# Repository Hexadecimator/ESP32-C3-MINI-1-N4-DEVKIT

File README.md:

# ESP32-C3-MINI-1-N4-DEVKIT
Custom ESP32-C3-MINI-1-N4 board devkit

Rev1 Layout Rendering:

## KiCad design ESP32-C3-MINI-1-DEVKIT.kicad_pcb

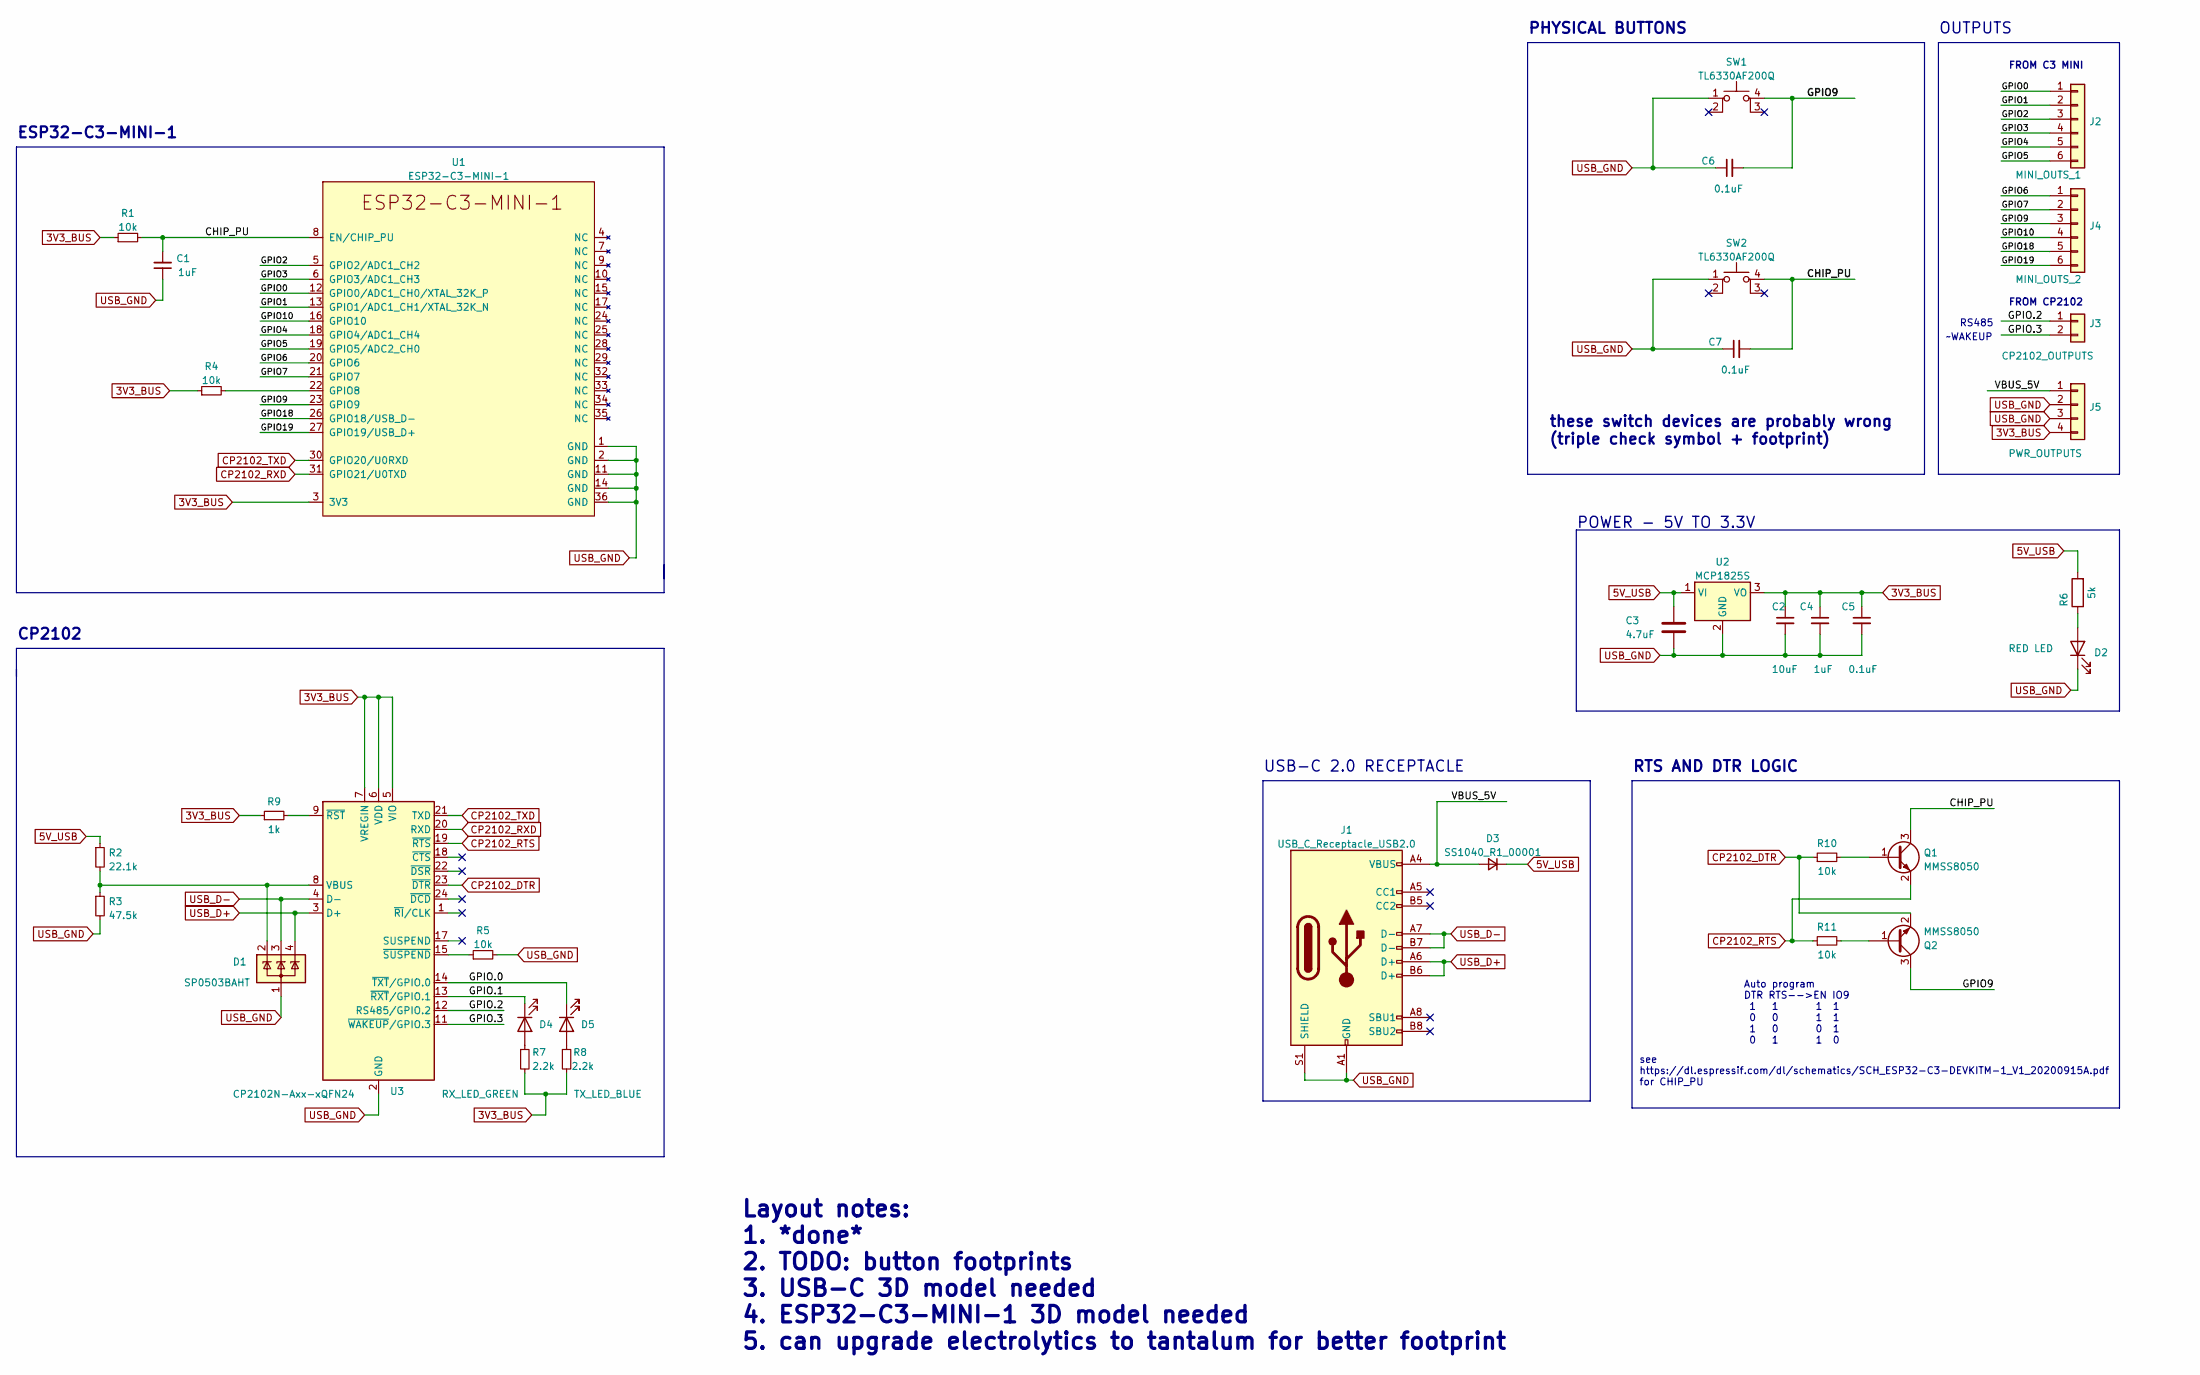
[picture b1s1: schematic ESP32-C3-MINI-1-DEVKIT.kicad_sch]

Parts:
C1, C4: 1uF; C_0805_2012Metric
C2: 10uF; CP_Elec_5x5.3
C3: 4.7uF; CP_Elec_5x5.3
C5, C6, C7: 0.1uF; C_0805_2012Metric
D1: SP0503BAHT; SOT-143
D2: RED LED; LED_0603_1608Metric
D3: SS1040_R1_00001; D_SOD-123
D4: RX_LED_GREEN; LED_0603_1608Metric
D5: TX_LED_BLUE; LED_0603_1608Metric
J1: USB_C_Receptacle_USB2.0; USB_C_Receptacle_HRO_TYPE-C-31-M-12
J2: MINI_OUTS_1; PinHeader_1x06_P2.54mm_Vertical
J3: CP2102_OUTPUTS; PinHeader_1x02_P2.54mm_Vertical
J4: MINI_OUTS_2; PinHeader_1x06_P2.54mm_Vertical
J5: PWR_OUTPUTS; PinHeader_1x04_P2.54mm_Vertical
Q1, Q2: MMSS8050; SOT-23
R1, R4, R5, R10, R11: 10k; R_0805_2012Metric
R2: 22.1k; R_0805_2012Metric
R3: 47.5k; R_0805_2012Metric
R6: 5k; R_0805_2012Metric
R7, R8: 2.2k; R_0805_2012Metric
R9: 1k; R_0805_2012Metric
SW1, SW2: TL6330AF200Q; SW_Push_1P1T_NO_CK_KMR2
U1: ESP32-C3-MINI-1
U2: MCP1825S; SOT-223-3_TabPin2
U3: CP2102N-Axx-xQFN24; QFN-24-1EP_4x4mm_P0.5mm_EP2.6x2.6mm

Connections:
3V3_BUS: C2.1, C4.1, C5.1, J5.4, R1.1, R4.1, R7.2, R8.2, R9.1, U1.3 (3V3), U2.3 (VO), U3.5 (VIO), U3.6 (VDD), U3.7 (VREGIN)
5V_USB: C3.1, D3.1 (K), R2.1, R6.2, U2.1 (VI)
/CHIP_PU: C1.2, C7.2, Q1.3 (C), R1.2, SW2.4 (A), U1.8 (EN/CHIP_PU)
/GPIO0: J2.1, U1.12 (GPIO0/ADC1_CH0/XTAL_32K_P)
/GPIO1: J2.2, U1.13 (GPIO1/ADC1_CH1/XTAL_32K_N)
/GPIO2: J2.3, U1.5 (GPIO2/ADC1_CH2)
/GPIO3: J2.4, U1.6 (GPIO3/ADC1_CH3)
/GPIO4: J2.5, U1.18 (GPIO4/ADC1_CH4)
/GPIO5: J2.6, U1.19 (GPIO5/ADC2_CH0)
/GPIO6: J4.1, U1.20 (GPIO6)
/GPIO7: J4.2, U1.21 (GPIO7)
/GPIO9: C6.2, J4.3, Q2.3 (C), SW1.4 (A), U1.23 (GPIO9)
/GPIO10: J4.4, U1.16 (GPIO10)
/GPIO18: J4.5, U1.26 (GPIO18/USB_D-)
/GPIO19: J4.6, U1.27 (GPIO19/USB_D+)
/GPIO.0: D5.1 (K), U3.14 (~TXT/GPIO.0)
/GPIO.1: D4.1 (K), U3.13 (~RXT/GPIO.1)
/GPIO.2: J3.1, U3.12 (RS485/GPIO.2)
/GPIO.3: J3.2, U3.11 (~WAKEUP/GPIO.3)
/VBUS_5V: D3.2 (A), J1.A4 (VBUS), J1.A9 (VBUS), J1.B4 (VBUS), J1.B9 (VBUS), J5.1
CP2102_DTR: Q2.2 (E), R10.1, U3.23 (~DTR)
CP2102_RTS: Q1.2 (E), R11.1, U3.19 (~RTS)
CP2102_RXD: U1.31 (GPIO21/U0TXD), U3.20 (RXD)
CP2102_TXD: U1.30 (GPIO20/U0RXD), U3.21 (TXD)
unnamed: D1.2 (K), R2.2, R3.1, U3.8 (VBUS)
unnamed: D2.2 (A), R6.1
unnamed: D4.2 (A), R7.1
unnamed: D5.2 (A), R8.1
unnamed: Q1.1 (B), R10.2
unnamed: Q2.1 (B), R11.2
unnamed: R4.2, U1.22 (GPIO8)
unnamed: R5.1, U3.15 (~SUSPEND)
unnamed: R9.2, U3.9 (~RST)
USB_D+: D1.4 (K), J1.A6 (D+), J1.B6 (D+), U3.3 (D+)
USB_D-: D1.3 (K), J1.A7 (D-), J1.B7 (D-), U3.4 (D-)
USB_GND: C1.1, C2.2, C3.2, C4.2, C5.2, C6.1, C7.1, D1.1 (A), D2.1 (K), J1.A1 (GND), J1.A12 (GND), J1.B1 (GND), J1.B12 (GND), J1.S1 (SHIELD), J5.2, J5.3, R3.2, R5.2, SW1.1, SW2.1, U1.1 (GND), U1.2 (GND), U1.11 (GND), U1.14 (GND), U1.36 (GND), U2.2 (GND), U3.2 (GND), U3.25 (GND)

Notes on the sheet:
these switch devices are probably wrong (triple check symbol + footprint)
Auto program DTR RTS-->EN IO9 1 1 1 1 0 0 1 1 1 0 0 1 0 1 1 0
USB-C 2.0 RECEPTACLE
POWER - 5V TO 3.3V
Layout notes: 1. *done* 2. TODO: button footprints 3. USB-C 3D model needed 4. ESP32-C3-MINI-1 3D model needed 5. can upgrade electrolytics to tantalum for better footprint
FROM CP2102
see https://dl.espressif.com/dl/schematics/SCH_ESP32-C3-DEVKITM-1_V1_20200915A.pdf for CHIP_PU
~WAKEUP
CP2102
RTS AND DTR LOGIC
PHYSICAL BUTTONS
FROM C3 MINI
RS485
OUTPUTS
ESP32-C3-MINI-1

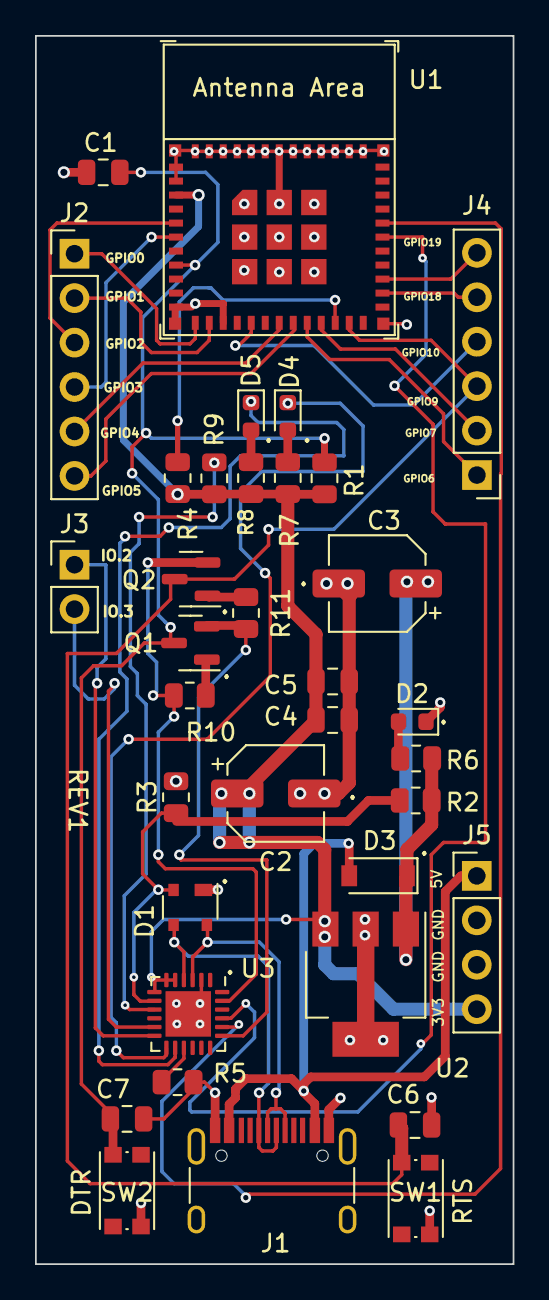
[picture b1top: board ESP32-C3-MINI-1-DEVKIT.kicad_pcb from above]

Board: 2 copper layers, 27.3 x 70.2 mm, 35 parts (0 on the bottom side), 36 nets.

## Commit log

2022-07-05 mostly done with cp2102
2022-07-06 Schematic v1 finished(?)
    schematic finished and pcb layout ready to start for first time. schematic will very likely change
2022-07-13 lots of updates, started layout
2022-07-14 layout continues
2022-07-17 layout progress
2022-07-18 layout finished, does not pass DRC
    need to revise and pass DRC now
2022-07-18 add image
2022-07-18 spacing
2022-07-18 passes DRC
2022-07-18 added image back
2022-07-18 updated after passing DRC
2022-07-18 silkscreen done
2022-07-18 mirrored back solder mask text
2022-07-18 board ready for JLCPCB
    board has been printed out on paper and parts have been dry-fit and everything seems to be good, ready to order
